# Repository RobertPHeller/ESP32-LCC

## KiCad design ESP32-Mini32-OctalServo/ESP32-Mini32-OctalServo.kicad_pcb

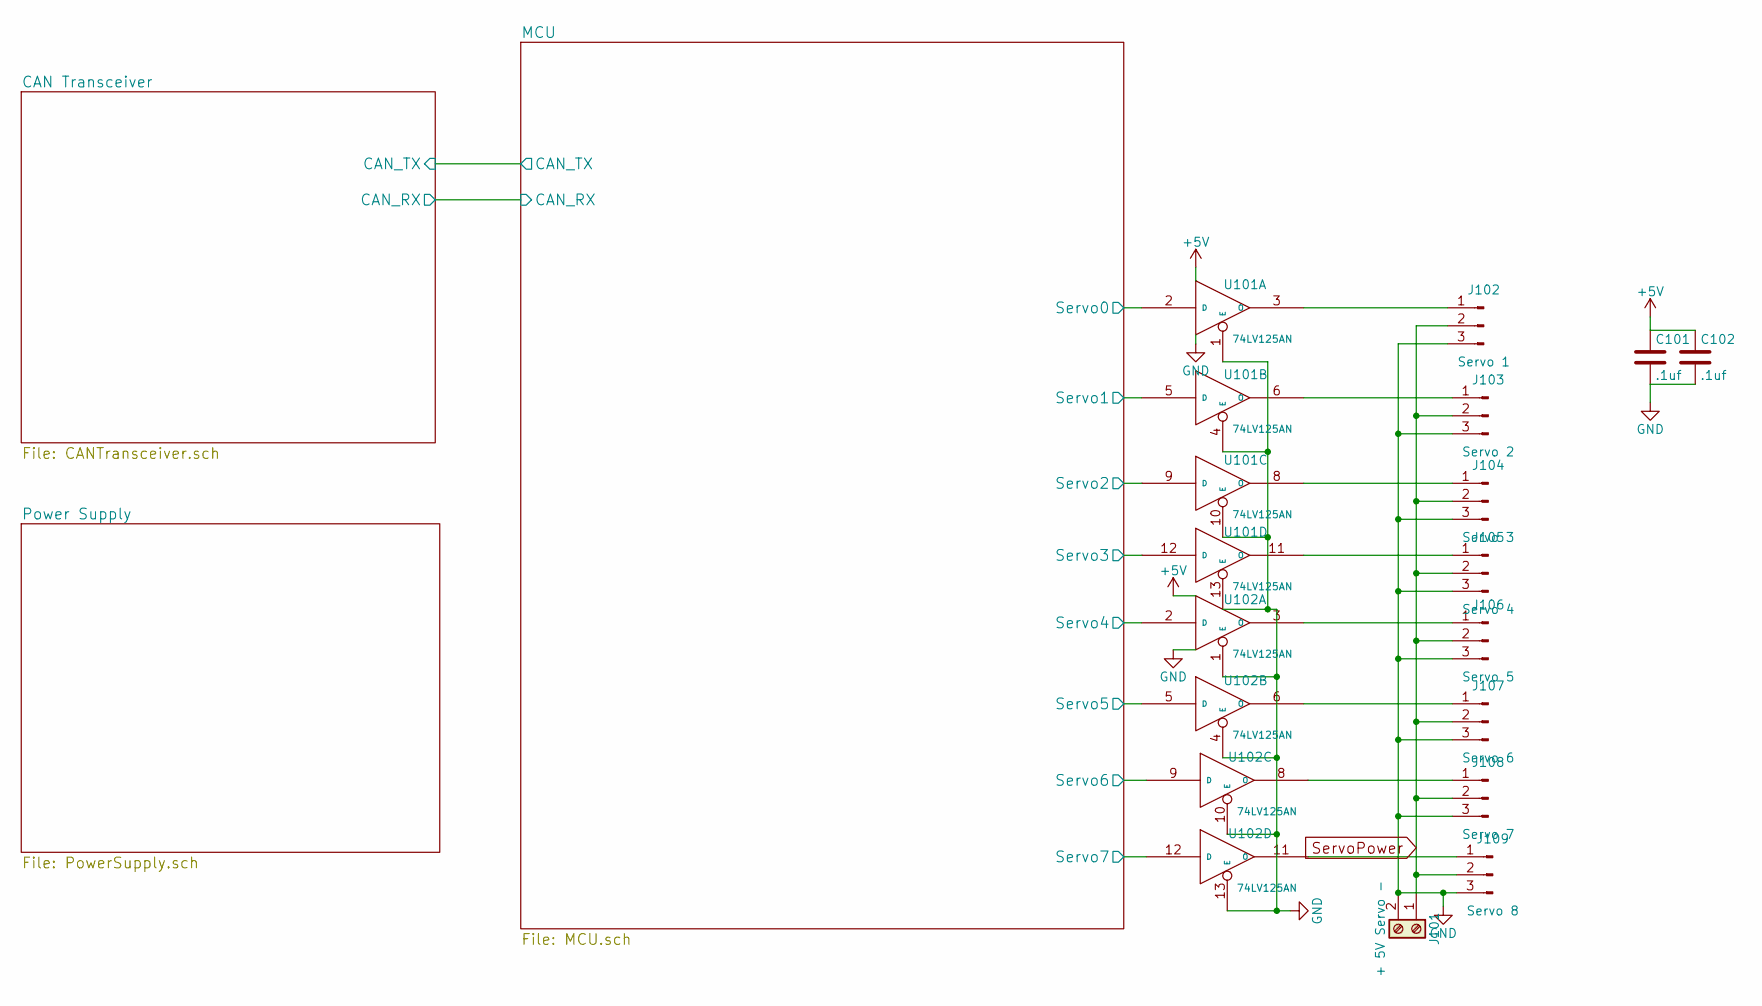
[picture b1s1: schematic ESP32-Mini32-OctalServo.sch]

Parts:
C101, C102: .1uf; C_0603
J101: + 5V Servo -; TerminalBlock_Pheonix_PT-3.5mm_2pol
J102: Servo 1; Pin_Header_Straight_1x03_Pitch2.54mm
J103: Servo 2; Pin_Header_Straight_1x03_Pitch2.54mm
J104: Servo 3; Pin_Header_Straight_1x03_Pitch2.54mm
J105: Servo 4; Pin_Header_Straight_1x03_Pitch2.54mm
J106: Servo 5; Pin_Header_Straight_1x03_Pitch2.54mm
J107: Servo 6; Pin_Header_Straight_1x03_Pitch2.54mm
J108: Servo 7; Pin_Header_Straight_1x03_Pitch2.54mm
J109: Servo 8; Pin_Header_Straight_1x03_Pitch2.54mm
U101, U102: 74LV125AN; SOIC-14_3.9x8.7mm_Pitch1.27mm; Mouser Part Number 771-AHCT125D118

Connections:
+5V: C101.1, C102.1, U101.14 (VCC), U102.14 (VCC); also elsewhere on the board
/MCU/Servo0: U101.2 (D); also elsewhere on the board
/MCU/Servo1: U101.5 (D); also elsewhere on the board
/MCU/Servo2: U101.9 (D); also elsewhere on the board
/MCU/Servo3: U101.12 (D); also elsewhere on the board
/MCU/Servo4: U102.2 (D); also elsewhere on the board
/MCU/Servo5: U102.5 (D); also elsewhere on the board
/MCU/Servo6: U102.9 (D); also elsewhere on the board
/MCU/Servo7: U102.12 (D); also elsewhere on the board
GND: C101.2, C102.2, J101.2, J102.3, J103.3, J104.3, J105.3, J106.3, J107.3, J108.3, J109.3, U101.1 (E), U101.4 (E), U101.7 (GND), U101.10 (E), U101.13 (E), U102.1 (E), U102.4 (E), U102.7 (GND), U102.10 (E), U102.13 (E); also elsewhere on the board
unnamed: J102.1, U101.3 (O)
unnamed: J103.1, U101.6 (O)
unnamed: J104.1, U101.8 (O)
unnamed: J105.1, U101.11 (O)
unnamed: J106.1, U102.3 (O)
unnamed: J107.1, U102.6 (O)
unnamed: J108.1, U102.8 (O)
unnamed: J109.1, U102.11 (O)
ServoPower: J101.1, J102.2, J103.2, J104.2, J105.2, J106.2, J107.2, J108.2, J109.2

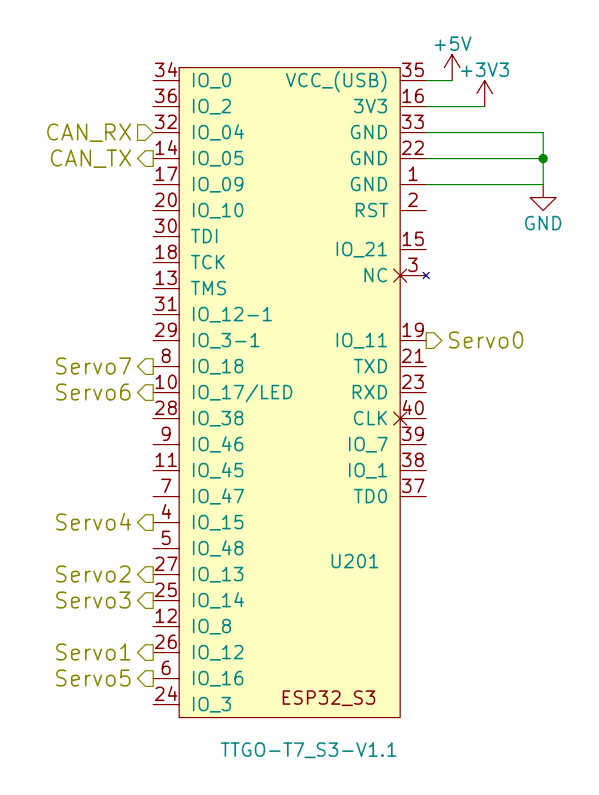
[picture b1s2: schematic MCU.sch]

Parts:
U201: TTGO-T7_S3-V1.1; ESP32_mini

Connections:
+3V3: U201.16 (3V3); also elsewhere on the board
+5V: U201.35 (VCC_(USB)); also elsewhere on the board
/CAN Transceiver/CAN_RX: U201.32 (IO_04); also elsewhere on the board
/CAN Transceiver/CAN_TX: U201.14 (IO_05); also elsewhere on the board
/MCU/Servo0: U201.19 (IO_11); also elsewhere on the board
/MCU/Servo1: U201.26 (IO_12); also elsewhere on the board
/MCU/Servo2: U201.27 (IO_13); also elsewhere on the board
/MCU/Servo3: U201.25 (IO_14); also elsewhere on the board
/MCU/Servo4: U201.4 (IO_15); also elsewhere on the board
/MCU/Servo5: U201.6 (IO_16); also elsewhere on the board
/MCU/Servo6: U201.10 (IO_17/LED); also elsewhere on the board
/MCU/Servo7: U201.8 (IO_18); also elsewhere on the board
GND: U201.1 (GND), U201.22 (GND), U201.33 (GND); also elsewhere on the board

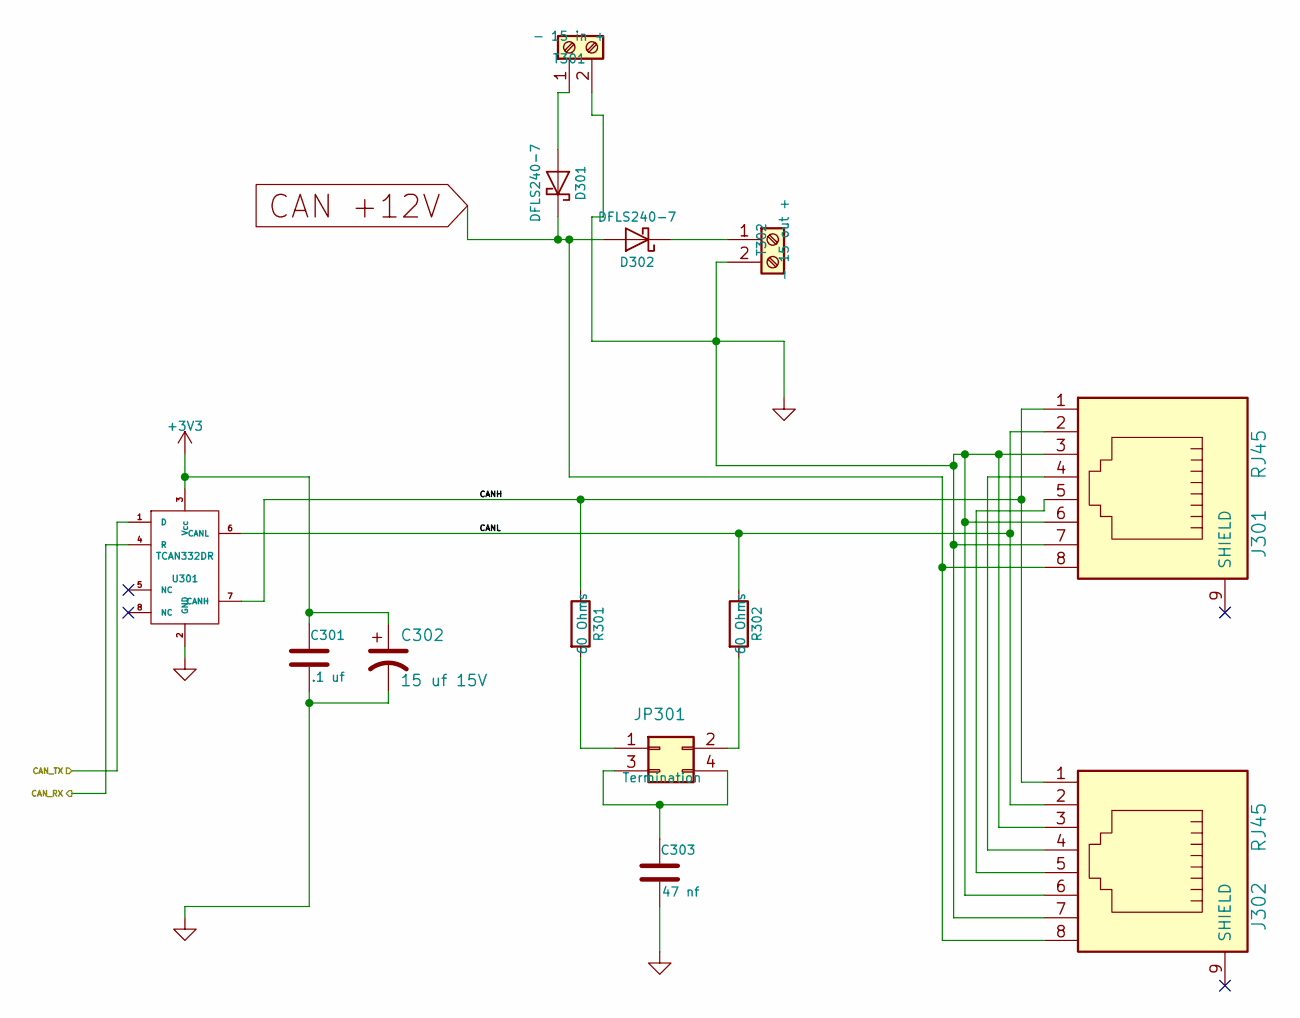
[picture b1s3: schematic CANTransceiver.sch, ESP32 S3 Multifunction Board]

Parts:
C301: .1 uf; C_0603; Mouser Part Number 710-885012206095
C302: 15 uf 15V; CP_Elec_4x5.7; Mouser Part Number 647-UUD1C150MCL
C303: 47 nf; C_0603; Mouser Part Number 710-885012206093
D301, D302: DFLS240-7; D_PowerDI-123; Mouser Part Number 621-DFLS240-7
J301, J302: RJ45; RJ45_8N-S; Mouser Part Number 710-615008144221
JP301: Termination; Pin_Header_Straight_2x02_Pitch2.54mm; Mouser Part Number 649-67997-404HLF
R301, R302: 60 Ohms; R_1206; Mouser Part Number 71-CRCW120660R0KNAIF
T301: - 15 in +; TerminalBlock_Pheonix_MPT-2.54mm_2pol; Mouser Part Number 651-1725656
T302: - 15 out +; TerminalBlock_Pheonix_MPT-2.54mm_2pol; Mouser Part Number 651-1725656
U301: TCAN332DR; SOIC-8_3.9x4.9mm_Pitch1.27mm; Mouser Part Number 595-TCAN332DR

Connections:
+3V3: C301.1, C302.1, U301.3 (Vcc); also elsewhere on the board
/CAN Transceiver/CANH: J301.1, J302.1, R301.1, U301.7 (CANH)
/CAN Transceiver/CANL: J301.2, J302.2, R302.1, U301.6 (CANL)
/CAN Transceiver/CAN_RX: U301.4 (R); also elsewhere on the board
/CAN Transceiver/CAN_TX: U301.1 (D); also elsewhere on the board
CAN +12V: D301.1 (K), D302.2 (A), J301.8, J302.8; also elsewhere on the board
GND: C301.2, C302.2, C303.2, J301.3, J301.6, J301.7, J302.3, J302.6, J302.7, T301.2, T302.2, U301.2 (GND); also elsewhere on the board
unnamed: C303.1, JP301.3, JP301.4
unnamed: D301.2 (A), T301.1
unnamed: D302.1 (K), T302.1
unnamed: J301.4, J302.4
unnamed: J301.5, J302.5
unnamed: JP301.1, R301.2
unnamed: JP301.2, R302.2

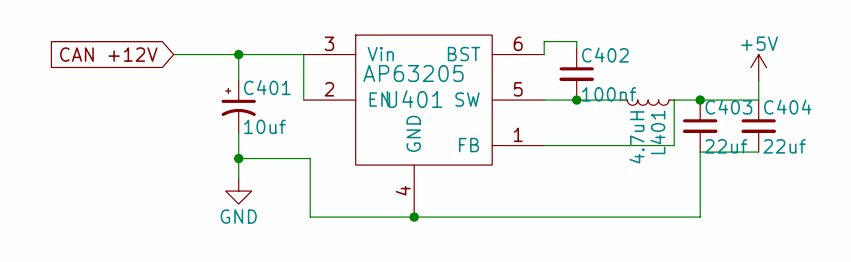
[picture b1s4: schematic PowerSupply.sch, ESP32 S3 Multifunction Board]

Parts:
C401: 10uf; CP_Elec_5x5.3; Mouser Part Number 710-865230542002
C402: 100nf; C_0603; Mouser Part Number 710-885012206020
C403, C404: 22uf; C_0603; Mouser Part Number 603-CC0603MRX6S5B226
L401: 4.7uH; L_7.3x7.3_H4.5; Mouser Part Number 81-B1047AS-4R7NP3
U401: AP63205; TSOT-23-6_MK06A; Mouser Part Number 621-AP63205WU-7

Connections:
+5V: C403.1, C404.1, L401.1, U401.1 (FB); also elsewhere on the board
CAN +12V: C401.1, U401.2 (EN), U401.3 (Vin); also elsewhere on the board
GND: C401.2, C403.2, C404.2, U401.4 (GND); also elsewhere on the board
unnamed: C402.1, U401.6 (BST)
unnamed: C402.2, L401.2, U401.5 (SW)

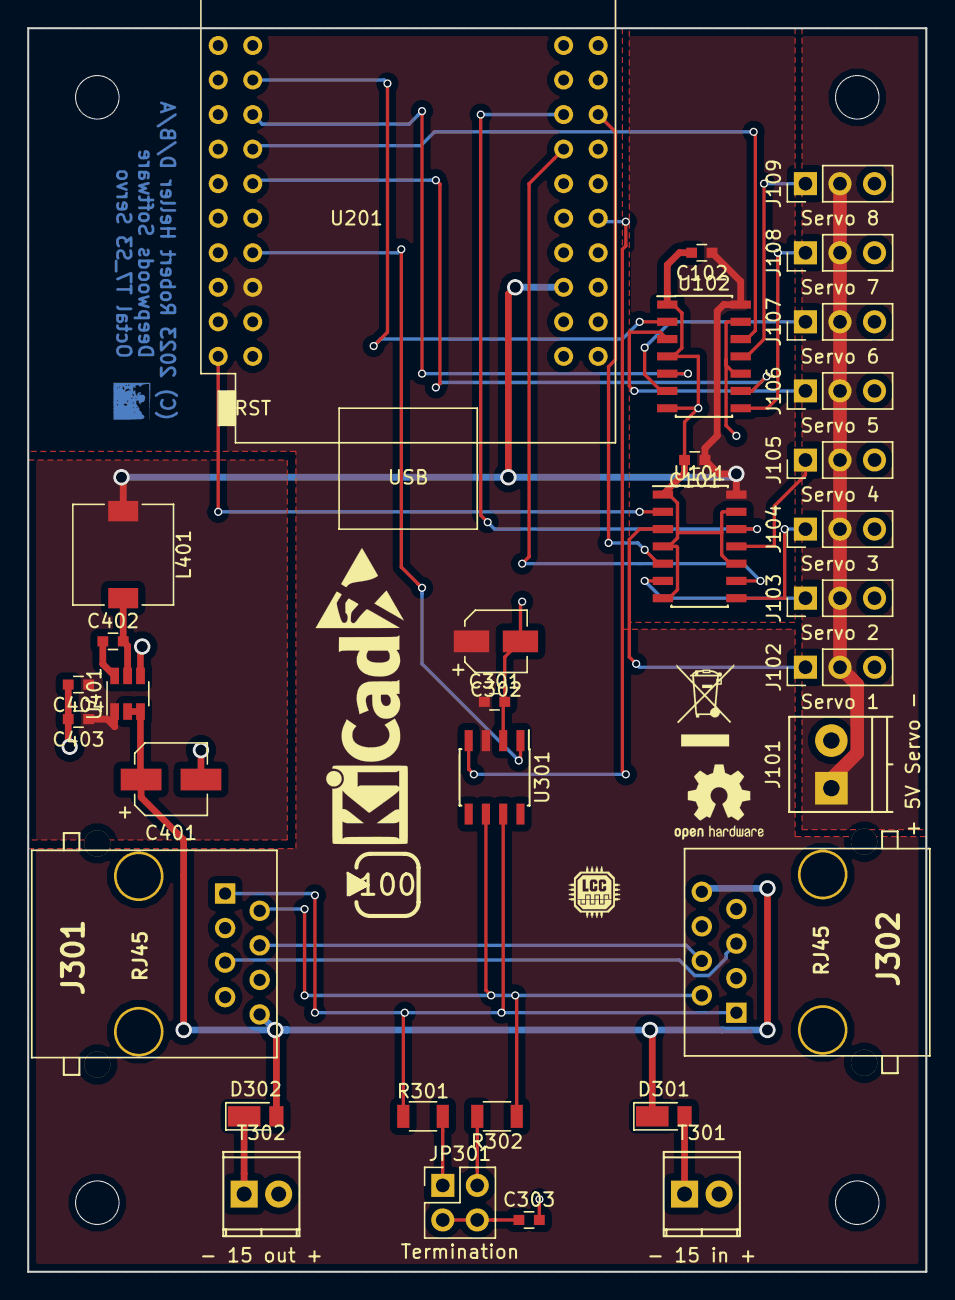
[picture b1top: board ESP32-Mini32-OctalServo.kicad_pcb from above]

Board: 2 copper layers, 66.0 x 91.4 mm, 33 parts (0 on the bottom side), 34 nets.

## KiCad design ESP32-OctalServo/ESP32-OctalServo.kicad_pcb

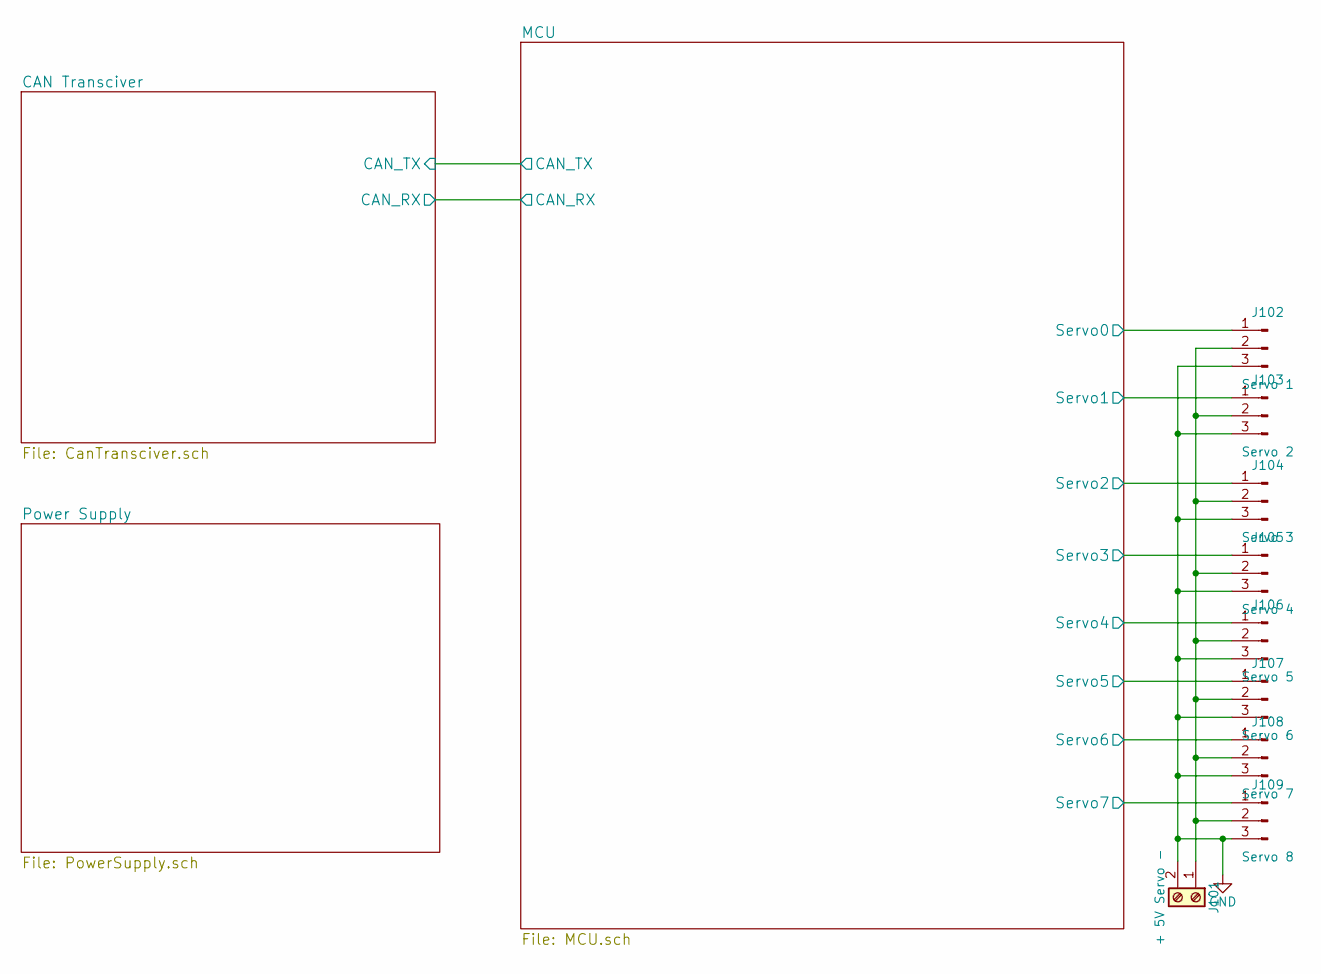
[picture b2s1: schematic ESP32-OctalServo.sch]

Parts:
J101: + 5V Servo -; TerminalBlock_Pheonix_PT-3.5mm_2pol
J102: Servo 1; Pin_Header_Straight_1x03_Pitch2.54mm
J103: Servo 2; Pin_Header_Straight_1x03_Pitch2.54mm
J104: Servo 3; Pin_Header_Straight_1x03_Pitch2.54mm
J105: Servo 4; Pin_Header_Straight_1x03_Pitch2.54mm
J106: Servo 5; Pin_Header_Straight_1x03_Pitch2.54mm
J107: Servo 6; Pin_Header_Straight_1x03_Pitch2.54mm
J108: Servo 7; Pin_Header_Straight_1x03_Pitch2.54mm
J109: Servo 8; Pin_Header_Straight_1x03_Pitch2.54mm

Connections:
/MCU/Servo0: J102.1; also elsewhere on the board
/MCU/Servo1: J103.1; also elsewhere on the board
/MCU/Servo2: J104.1; also elsewhere on the board
/MCU/Servo3: J105.1; also elsewhere on the board
/MCU/Servo4: J106.1; also elsewhere on the board
/MCU/Servo5: J107.1; also elsewhere on the board
/MCU/Servo6: J108.1; also elsewhere on the board
/MCU/Servo7: J109.1; also elsewhere on the board
GND: J101.2, J102.3, J103.3, J104.3, J105.3, J106.3, J107.3, J108.3, J109.3; also elsewhere on the board
unnamed: J101.1, J102.2, J103.2, J104.2, J105.2, J106.2, J107.2, J108.2, J109.2

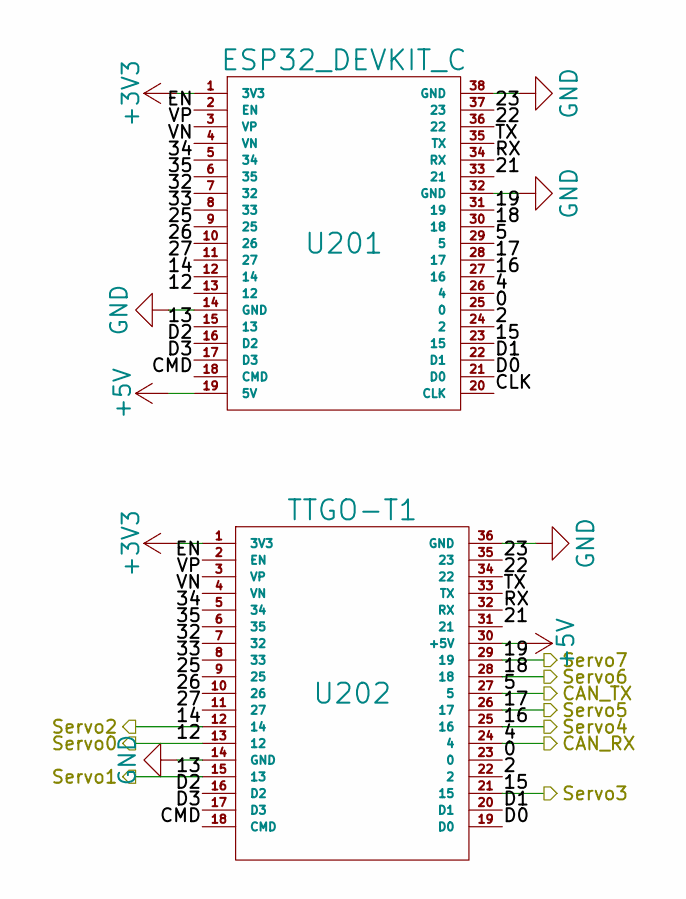
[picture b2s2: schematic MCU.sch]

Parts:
U201: ESP32_DEVKIT_C; ESP32-Devkit-C
U202: TTGO-T1; TIGO-T1

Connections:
+3V3: U201.1 (3V3), U202.1 (3V3); also elsewhere on the board
+5V: U201.19 (5V), U202.30 (+5V); also elsewhere on the board
/CAN Transciver/CAN_RX: U201.26 (4), U202.24 (4); also elsewhere on the board
/CAN Transciver/CAN_TX: U201.29 (5), U202.27 (5); also elsewhere on the board
/MCU/0: U201.25 (0), U202.23 (0)
/MCU/2: U201.24 (2), U202.22 (2)
/MCU/21: U201.33 (21), U202.31 (21)
/MCU/22: U201.36 (22), U202.34 (22)
/MCU/23: U201.37 (23), U202.35 (23)
/MCU/25: U201.9 (25), U202.9 (25)
/MCU/26: U201.10 (26), U202.10 (26)
/MCU/27: U201.11 (27), U202.11 (27)
/MCU/32: U201.7 (32), U202.7 (32)
/MCU/33: U201.8 (33), U202.8 (33)
/MCU/34: U201.5 (34), U202.5 (34)
/MCU/35: U201.6 (35), U202.6 (35)
/MCU/CLK: U201.20 (CLK)
/MCU/CMD: U201.18 (CMD), U202.18 (CMD)
/MCU/D0: U201.21 (D0), U202.19 (D0)
/MCU/D1: U201.22 (D1), U202.20 (D1)
/MCU/D2: U201.16 (D2), U202.16 (D2)
/MCU/D3: U201.17 (D3), U202.17 (D3)
/MCU/EN: U201.2 (EN), U202.2 (EN)
/MCU/RX: U201.34 (RX), U202.32 (RX)
/MCU/Servo0: U201.13 (12), U202.13 (12); also elsewhere on the board
/MCU/Servo1: U201.15 (13), U202.15 (13); also elsewhere on the board
/MCU/Servo2: U201.12 (14), U202.12 (14); also elsewhere on the board
/MCU/Servo3: U201.23 (15), U202.21 (15); also elsewhere on the board
/MCU/Servo4: U201.27 (16), U202.25 (16); also elsewhere on the board
/MCU/Servo5: U201.28 (17), U202.26 (17); also elsewhere on the board
/MCU/Servo6: U201.30 (18), U202.28 (18); also elsewhere on the board
/MCU/Servo7: U201.31 (19), U202.29 (19); also elsewhere on the board
/MCU/TX: U201.35 (TX), U202.33 (TX)
/MCU/VN: U201.4 (VN), U202.4 (VN)
/MCU/VP: U201.3 (VP), U202.3 (VP)
GND: U201.14 (GND), U201.32 (GND), U201.38 (GND), U202.14 (GND), U202.36 (GND); also elsewhere on the board

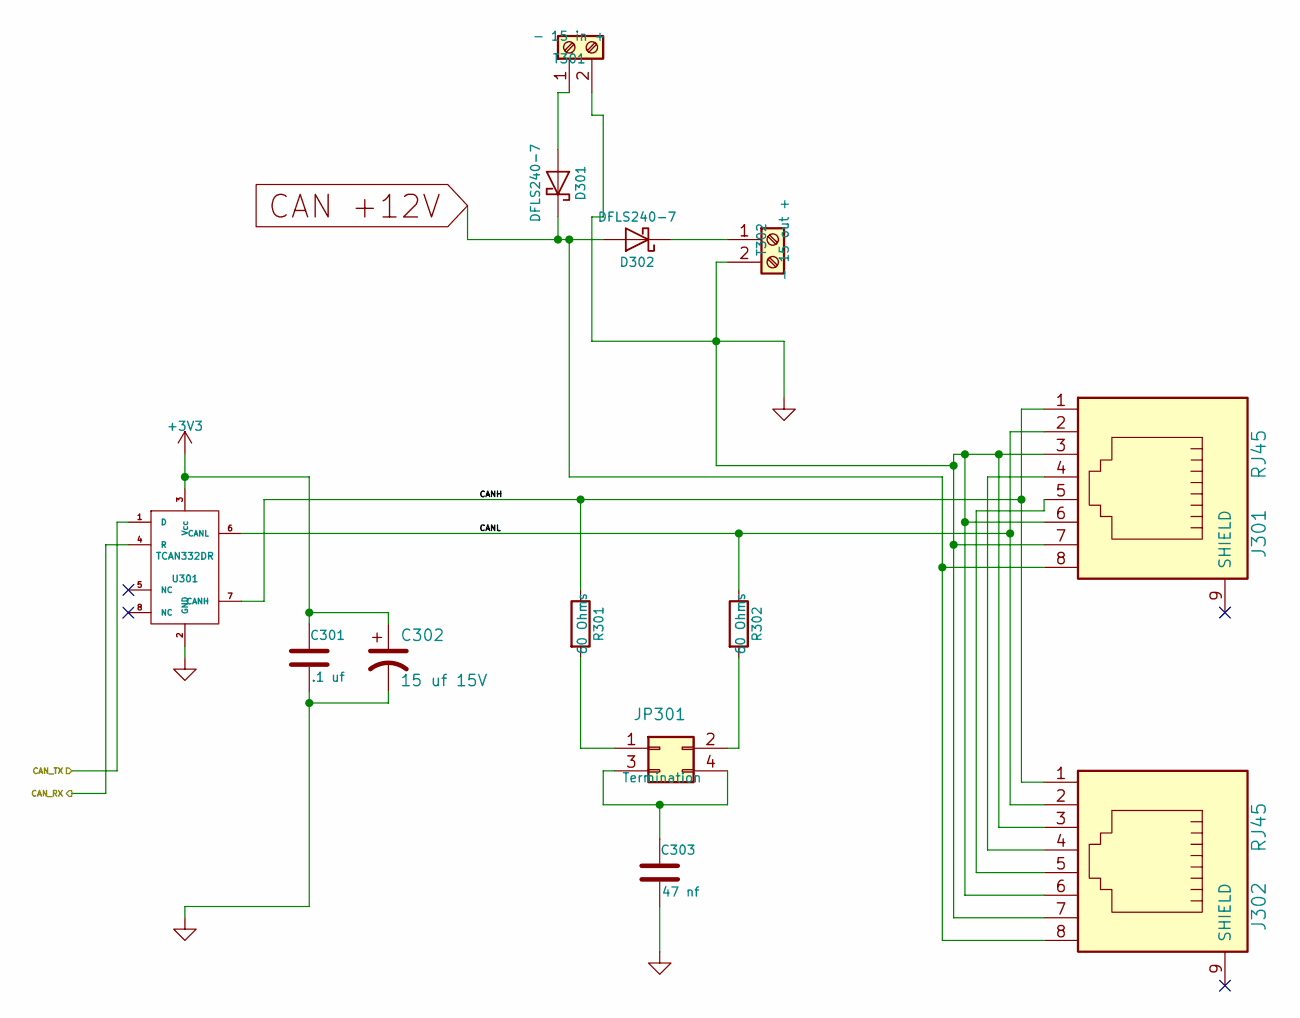
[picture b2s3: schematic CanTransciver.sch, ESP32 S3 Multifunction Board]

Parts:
C301: .1 uf; C_0603; Mouser Part Number 710-885012206095
C302: 15 uf 15V; CP_Elec_4x5.7; Mouser Part Number 647-UUD1C150MCL
C303: 47 nf; C_0603; Mouser Part Number 710-885012206093
D301, D302: DFLS240-7; D_PowerDI-123; Mouser Part Number 621-DFLS240-7
J301, J302: RJ45; RJ45_8N-S; Mouser Part Number 710-615008144221
JP301: Termination; Pin_Header_Straight_2x02_Pitch2.54mm; Mouser Part Number 649-67997-404HLF
R301, R302: 60 Ohms; R_1206; Mouser Part Number 71-CRCW120660R0KNAIF
T301: - 15 in +; TerminalBlock_Pheonix_MPT-2.54mm_2pol; Mouser Part Number 651-1725656
T302: - 15 out +; TerminalBlock_Pheonix_MPT-2.54mm_2pol; Mouser Part Number 651-1725656
U301: TCAN332DR; SOIC-8_3.9x4.9mm_Pitch1.27mm; Mouser Part Number 595-TCAN332DR

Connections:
+3V3: C301.1, C302.1, U301.3 (Vcc); also elsewhere on the board
/CAN Transciver/CANH: J301.1, J302.1, R301.1, U301.7 (CANH)
/CAN Transciver/CANL: J301.2, J302.2, R302.1, U301.6 (CANL)
/CAN Transciver/CAN_RX: U301.4 (R); also elsewhere on the board
/CAN Transciver/CAN_TX: U301.1 (D); also elsewhere on the board
CAN +12V: D301.1 (K), D302.2 (A), J301.8, J302.8; also elsewhere on the board
GND: C301.2, C302.2, C303.2, J301.3, J301.6, J301.7, J302.3, J302.6, J302.7, T301.2, T302.2, U301.2 (GND); also elsewhere on the board
unnamed: C303.1, JP301.3, JP301.4
unnamed: D301.2 (A), T301.1
unnamed: D302.1 (K), T302.1
unnamed: J301.4, J302.4
unnamed: J301.5, J302.5
unnamed: JP301.1, R301.2
unnamed: JP301.2, R302.2

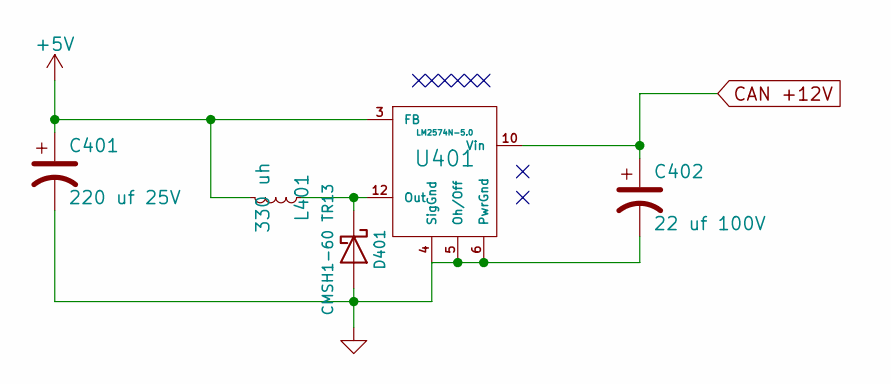
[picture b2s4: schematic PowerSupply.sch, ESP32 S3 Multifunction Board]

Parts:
C401: 220 uf 25V; CP_Elec_8x10; Mouser Part Number 647-UWT1E221MNL1GS
C402: 22 uf 100V; CP_Elec_8x10; Mouser Part Number 647-UUX2A220MNL6GS
D401: CMSH1-60 TR13; D_SMB; Mouser Part Number 610-CMSH1-60TR13
L401: 330 uh; SRN1060; Mouser Part Number 652-SRN1060-331M
U401: LM2574N-5.0; SOIC-14_7.4x8.7mm_Pitch1.27mm; Mouser Part Number 926-LM2574MX-5.0NOPB

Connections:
+5V: C401.1, L401.2, U401.3 (FB); also elsewhere on the board
CAN +12V: C402.1, U401.10 (Vin); also elsewhere on the board
GND: C401.2, C402.2, D401.2 (A), U401.4 (SigGnd), U401.5 (Oh/Off), U401.6 (PwrGnd); also elsewhere on the board
unnamed: D401.1 (K), L401.1, U401.12 (Out)

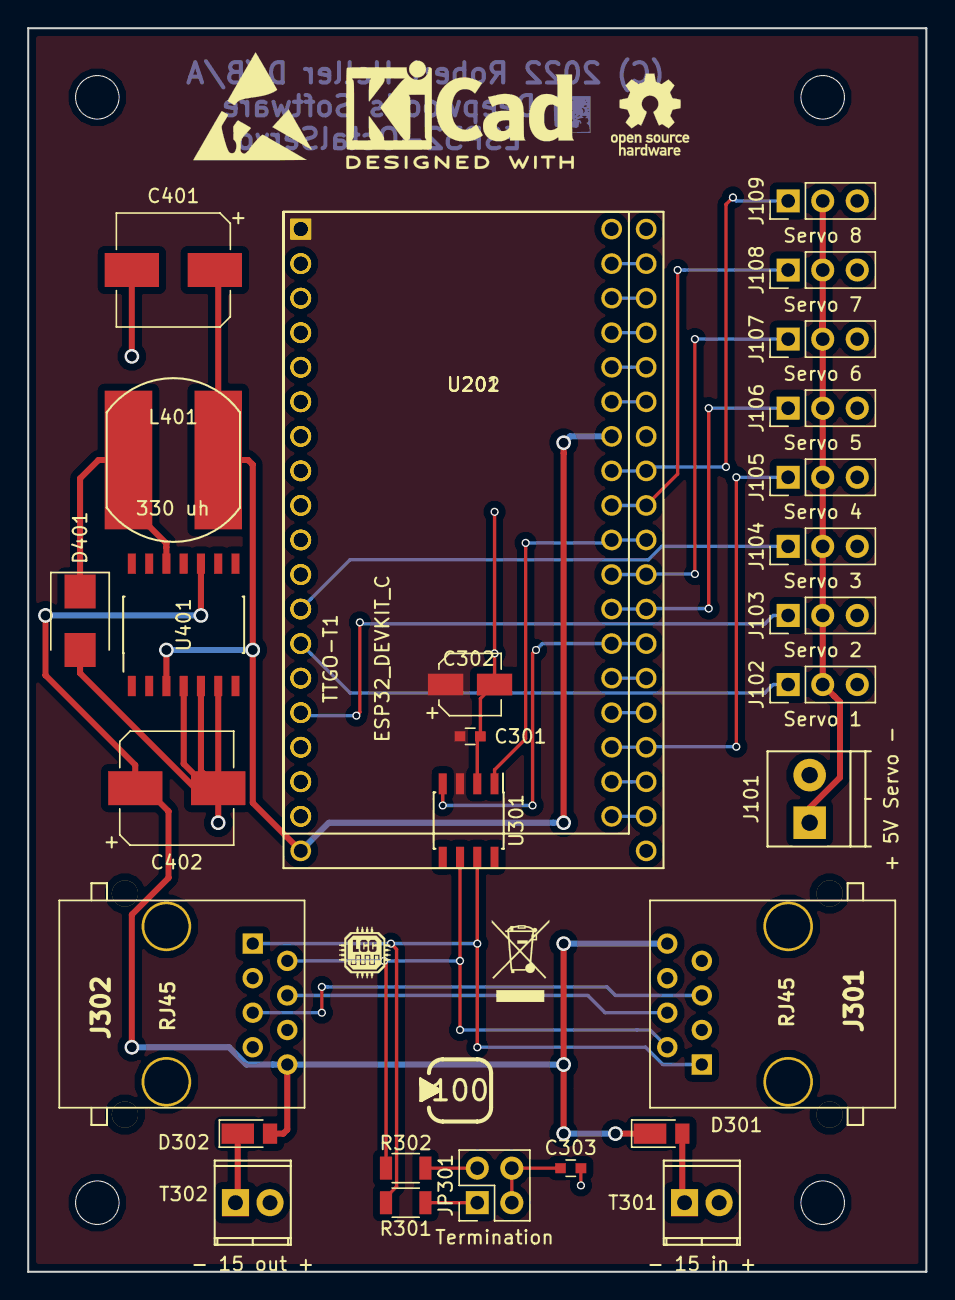
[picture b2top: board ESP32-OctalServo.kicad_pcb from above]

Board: 2 copper layers, 66.0 x 91.4 mm, 29 parts (0 on the bottom side), 47 nets.

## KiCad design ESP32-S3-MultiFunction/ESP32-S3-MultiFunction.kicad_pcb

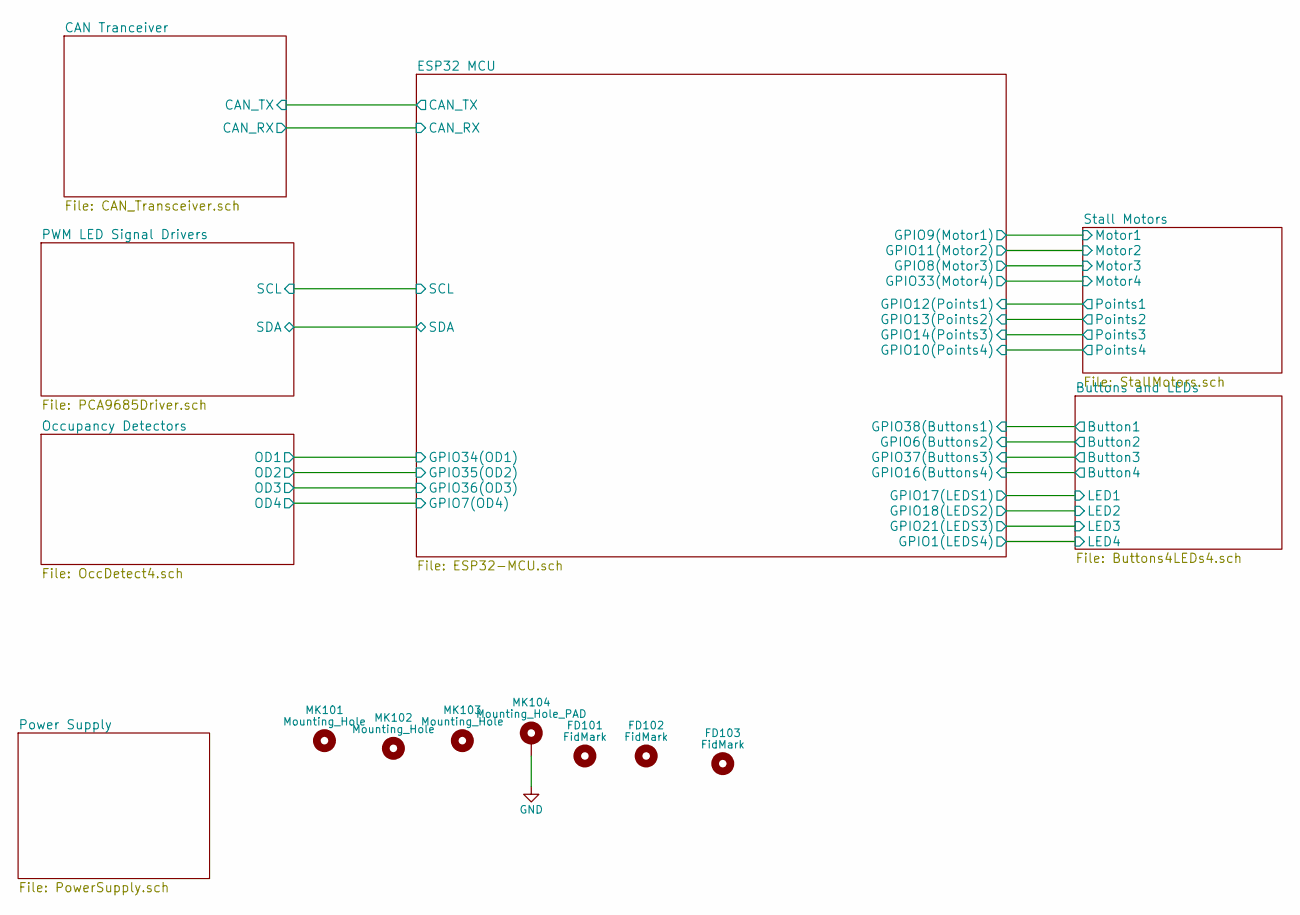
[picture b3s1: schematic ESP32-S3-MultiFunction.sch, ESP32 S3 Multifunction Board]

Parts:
FD101, FD102, FD103: FidMark; Fiducial_1mm_Dia_2.54mm_Outer_CopperTop
MK101, MK102, MK103: Mounting_Hole; MountingHole_3.7mm
MK104: Mounting_Hole_PAD; MountingHole_3.7mm_Pad

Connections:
GND: MK104.1; also elsewhere on the board

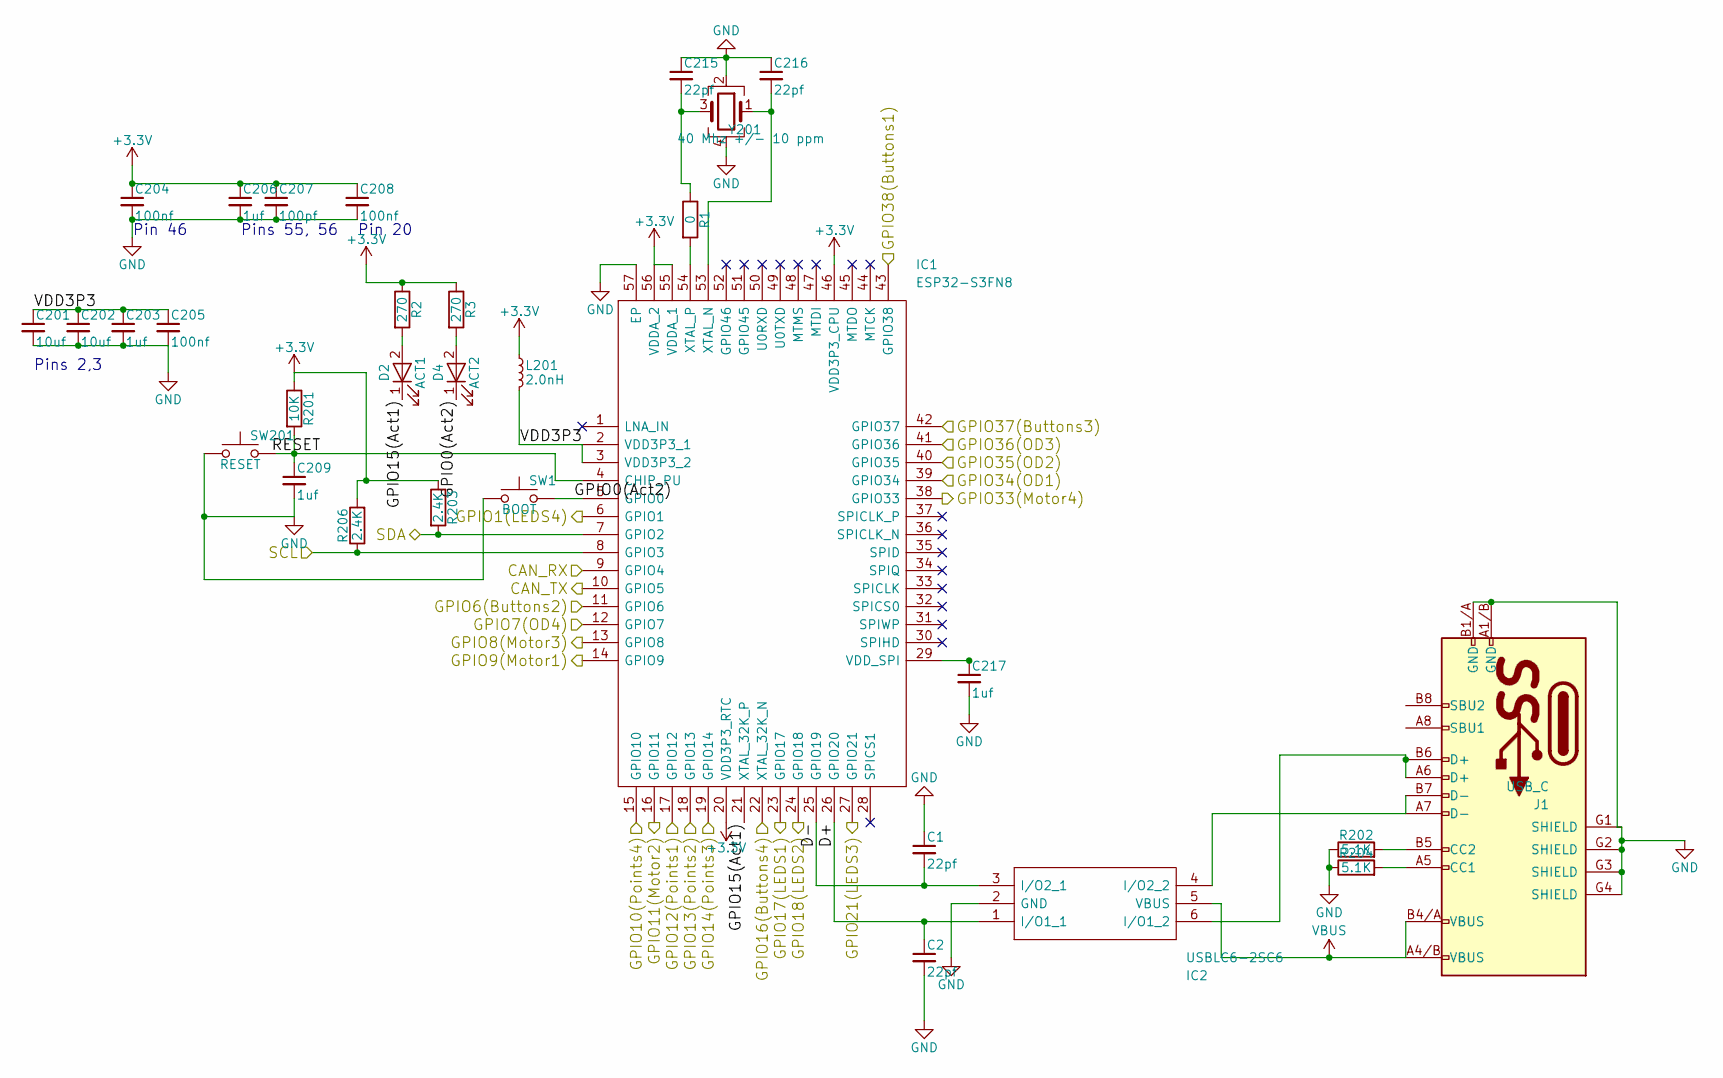
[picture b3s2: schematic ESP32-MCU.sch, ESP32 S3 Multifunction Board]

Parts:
C1, C2, C215, C216: 22pf; C_0402; Mouser Part Number 187-CL05C220JB5NNND
C201, C202: 10uf; C_0805; Mouser Part Number 187-CL21A106MQFNNNE
C203, C206, C209, C217: 1uf; C_0402; Mouser Part Number 80-C0402C101K8RAUTO
C204, C205, C208: 100nf; C_0402; Mouser Part Number 710-885012105001
C207: 100pf; C_0402; Mouser Part Number 80-C0402C101K3RAUTO
D2: ACT1; LED_0402; Mouser Part Number 710-150040GS73220
D4: ACT2; LED_0402; Mouser Part Number 710-150040SS73220
IC1: ESP32-S3FN8; QFN-56-1EP_7x7mm_Pitch0.4mm; Manufacturer_Part_Number ESP32-S3FN8; Mouser Part Number 356-ESP32-S3FN8
IC2: USBLC6-2SC6; SOT-23-6; Mouser Part Number 511-USBLC6-2SC6
J1: USB_C; GCT_USB4105-GF-A; Mouser Part Number 640-USB4105-GF-A-120
L201: 2.0nH; L_0402; Mouser Part Number 810-MLG1005S2N0ST000
R1: 0; R_0402; Mouser Part Number 71-CRCW04020000Z0EDC
R2, R3: 270; R_0402; Mouser Part Number 754-RR0510P-271D
R201: 10K; R_0402; Mouser Part Number 603-RC0402JR-1310KL
R202, R204: 5.1K; R_0402; Mouser Part Number 71-CRCW0402-5.1K-E3
R203, R206: 2.4K; R_0402; Mouser Part Number 71-CRCW06032K40JNEAC
SW1: BOOT; SW_SPST_B3U-1000P-B; Mouser Part Number 653-B3U-1000PM-B
SW201: RESET; SW_SPST_B3U-1000P-B; Mouser Part Number 653-B3U-1000PM-B
Y201: 40 Mhz +/- 10 ppm; FA20_H; Mouser Part Number 732-FA-20H40MF10Z-W3

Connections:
/Buttons and LEDs/Button1: IC1.43 (GPIO38); also elsewhere on the board
/Buttons and LEDs/Button2: IC1.11 (GPIO6); also elsewhere on the board
/Buttons and LEDs/Button3: IC1.42 (GPIO37); also elsewhere on the board
/Buttons and LEDs/Button4: IC1.22 (XTAL_32K_N); also elsewhere on the board
/CAN Tranceiver/CAN_RX: IC1.9 (GPIO4); also elsewhere on the board
/CAN Tranceiver/CAN_TX: IC1.10 (GPIO5); also elsewhere on the board
/ESP32 MCU/D+: C2.1, IC1.26 (GPIO20), IC2.1 (I/O1_1)
/ESP32 MCU/D-: C1.2, IC1.25 (GPIO19), IC2.3 (I/O2_1)
/ESP32 MCU/GPIO0(Act2): D4.1 (K), IC1.5 (GPIO0), SW1.2
/ESP32 MCU/GPIO1(LEDS4): IC1.6 (GPIO1); also elsewhere on the board
/ESP32 MCU/GPIO7(OD4): IC1.12 (GPIO7); also elsewhere on the board
/ESP32 MCU/GPIO8(Motor3): IC1.13 (GPIO8); also elsewhere on the board
/ESP32 MCU/GPIO9(Motor1): IC1.14 (GPIO9); also elsewhere on the board
/ESP32 MCU/GPIO10(Points4): IC1.15 (GPIO10); also elsewhere on the board
/ESP32 MCU/GPIO11(Motor2): IC1.16 (GPIO11); also elsewhere on the board
/ESP32 MCU/GPIO12(Points1): IC1.17 (GPIO12); also elsewhere on the board
/ESP32 MCU/GPIO13(Points2): IC1.18 (GPIO13); also elsewhere on the board
/ESP32 MCU/GPIO14(Points3): IC1.19 (GPIO14); also elsewhere on the board
/ESP32 MCU/GPIO15(Act1): D2.1 (K), IC1.21 (XTAL_32K_P)
/ESP32 MCU/GPIO17(LEDS1): IC1.23 (GPIO17); also elsewhere on the board
/ESP32 MCU/GPIO18(LEDS2): IC1.24 (GPIO18); also elsewhere on the board
/ESP32 MCU/GPIO21(LEDS3): IC1.27 (GPIO21); also elsewhere on the board
/ESP32 MCU/GPIO33(Motor4): IC1.38 (GPIO33); also elsewhere on the board
/ESP32 MCU/GPIO34(OD1): IC1.39 (GPIO34); also elsewhere on the board
/ESP32 MCU/GPIO35(OD2): IC1.40 (GPIO35); also elsewhere on the board
/ESP32 MCU/GPIO36(OD3): IC1.41 (GPIO36); also elsewhere on the board
/ESP32 MCU/RESET: C209.1, IC1.4 (CHIP_PU), R201.2, SW201.2
/ESP32 MCU/SCL: IC1.8 (GPIO3), R206.1; also elsewhere on the board
/ESP32 MCU/SDA: IC1.7 (GPIO2), R203.2; also elsewhere on the board
/ESP32 MCU/VDD3P3: C201.1, C202.1, C203.1, C205.1, IC1.2 (VDD3P3_1), IC1.3 (VDD3P3_2), L201.2
GND: C1.1, C2.2, C201.2, C202.2, C203.2, C204.2, C205.2, C206.2, C207.2, C208.2, C209.2, C215.1, C216.1, C217.2, IC1.57 (EP), IC2.2 (GND), J1.A1/B (GND), J1.B1/A (GND), J1.G1 (SHIELD), J1.G2 (SHIELD), J1.G3 (SHIELD), J1.G4 (SHIELD), R202.1, R204.1, SW1.1, SW201.1, Y201.2, Y201.4; also elsewhere on the board
unnamed: C215.2, R1.1, Y201.3
unnamed: C216.2, IC1.53 (XTAL_N), Y201.1
unnamed: C217.1, IC1.29 (VDD_SPI)
unnamed: D2.2 (A), R2.2
unnamed: D4.2 (A), R3.2
unnamed: IC1.54 (XTAL_P), R1.2
unnamed: IC2.4 (I/O2_2), J1.A7 (D-), J1.B7 (D-)
unnamed: IC2.6 (I/O1_2), J1.A6 (D+), J1.B6 (D+)
unnamed: J1.A5 (CC1), R204.2
unnamed: J1.B5 (CC2), R202.2
VBUS: IC2.5 (VBUS), J1.A4/B (VBUS), J1.B4/A (VBUS); also elsewhere on the board

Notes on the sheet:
Pins 2,3
Pin 46
Pins 55, 56
Pin 20

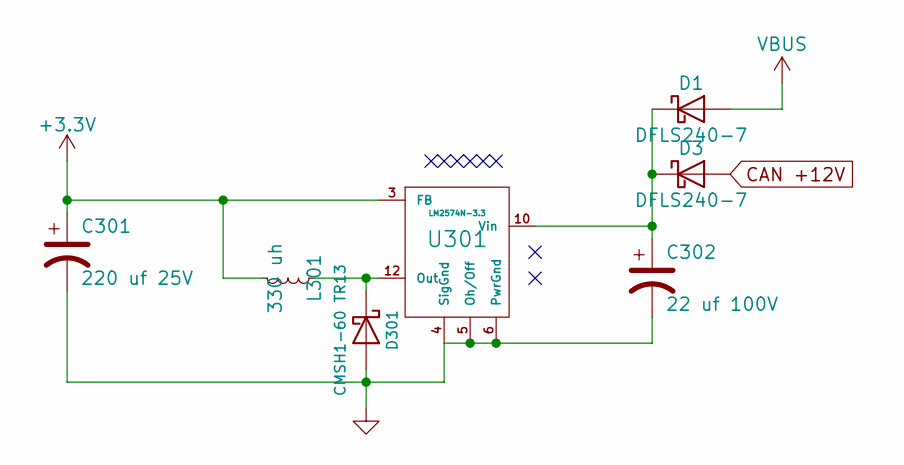
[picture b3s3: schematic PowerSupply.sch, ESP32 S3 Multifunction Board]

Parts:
C301: 220 uf 25V; CP_Elec_8x10; Mouser Part Number 647-UWT1E221MNL1GS
C302: 22 uf 100V; CP_Elec_8x10; Mouser Part Number 647-UUX2A220MNL6GS
D1, D3: DFLS240-7; D_PowerDI-123; Mouser Part Number 621-DFLS240-7
D301: CMSH1-60 TR13; D_SMB; Mouser Part Number 610-CMSH1-60TR13
L301: 330 uh; SRN1060; Mouser Part Number 652-SRN1060-331M
U301: LM2574N-3.3; SOIC-14_7.4x8.7mm_Pitch1.27mm; Mouser Part Number 926-LM2574MX33NOPB

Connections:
CAN +12V: D3.2 (A); also elsewhere on the board
GND: C301.2, C302.2, D301.2 (A), U301.4 (SigGnd), U301.5 (Oh/Off), U301.6 (PwrGnd); also elsewhere on the board
unnamed: C302.1, D1.1 (K), D3.1 (K), U301.10 (Vin)
unnamed: D301.1 (K), L301.1, U301.12 (Out)
VBUS: D1.2 (A); also elsewhere on the board

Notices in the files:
ESP32-Mini32-OctalServo/ESP32-Mini32-OctalServo.kicad_pcb:
(C) 2023 Robert Heller D/B/A
ESP32-OctalServo/ESP32-OctalServo.kicad_pcb:
(C) 2022 Robert Heller D/B/A
ESP32-S3-MultiFunction/ESP32-S3-MultiFunction.kicad_pcb:
(c) Copyright 2022 Robert Heller
